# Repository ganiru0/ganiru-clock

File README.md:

# ganiru-clock
 my first HPS clock

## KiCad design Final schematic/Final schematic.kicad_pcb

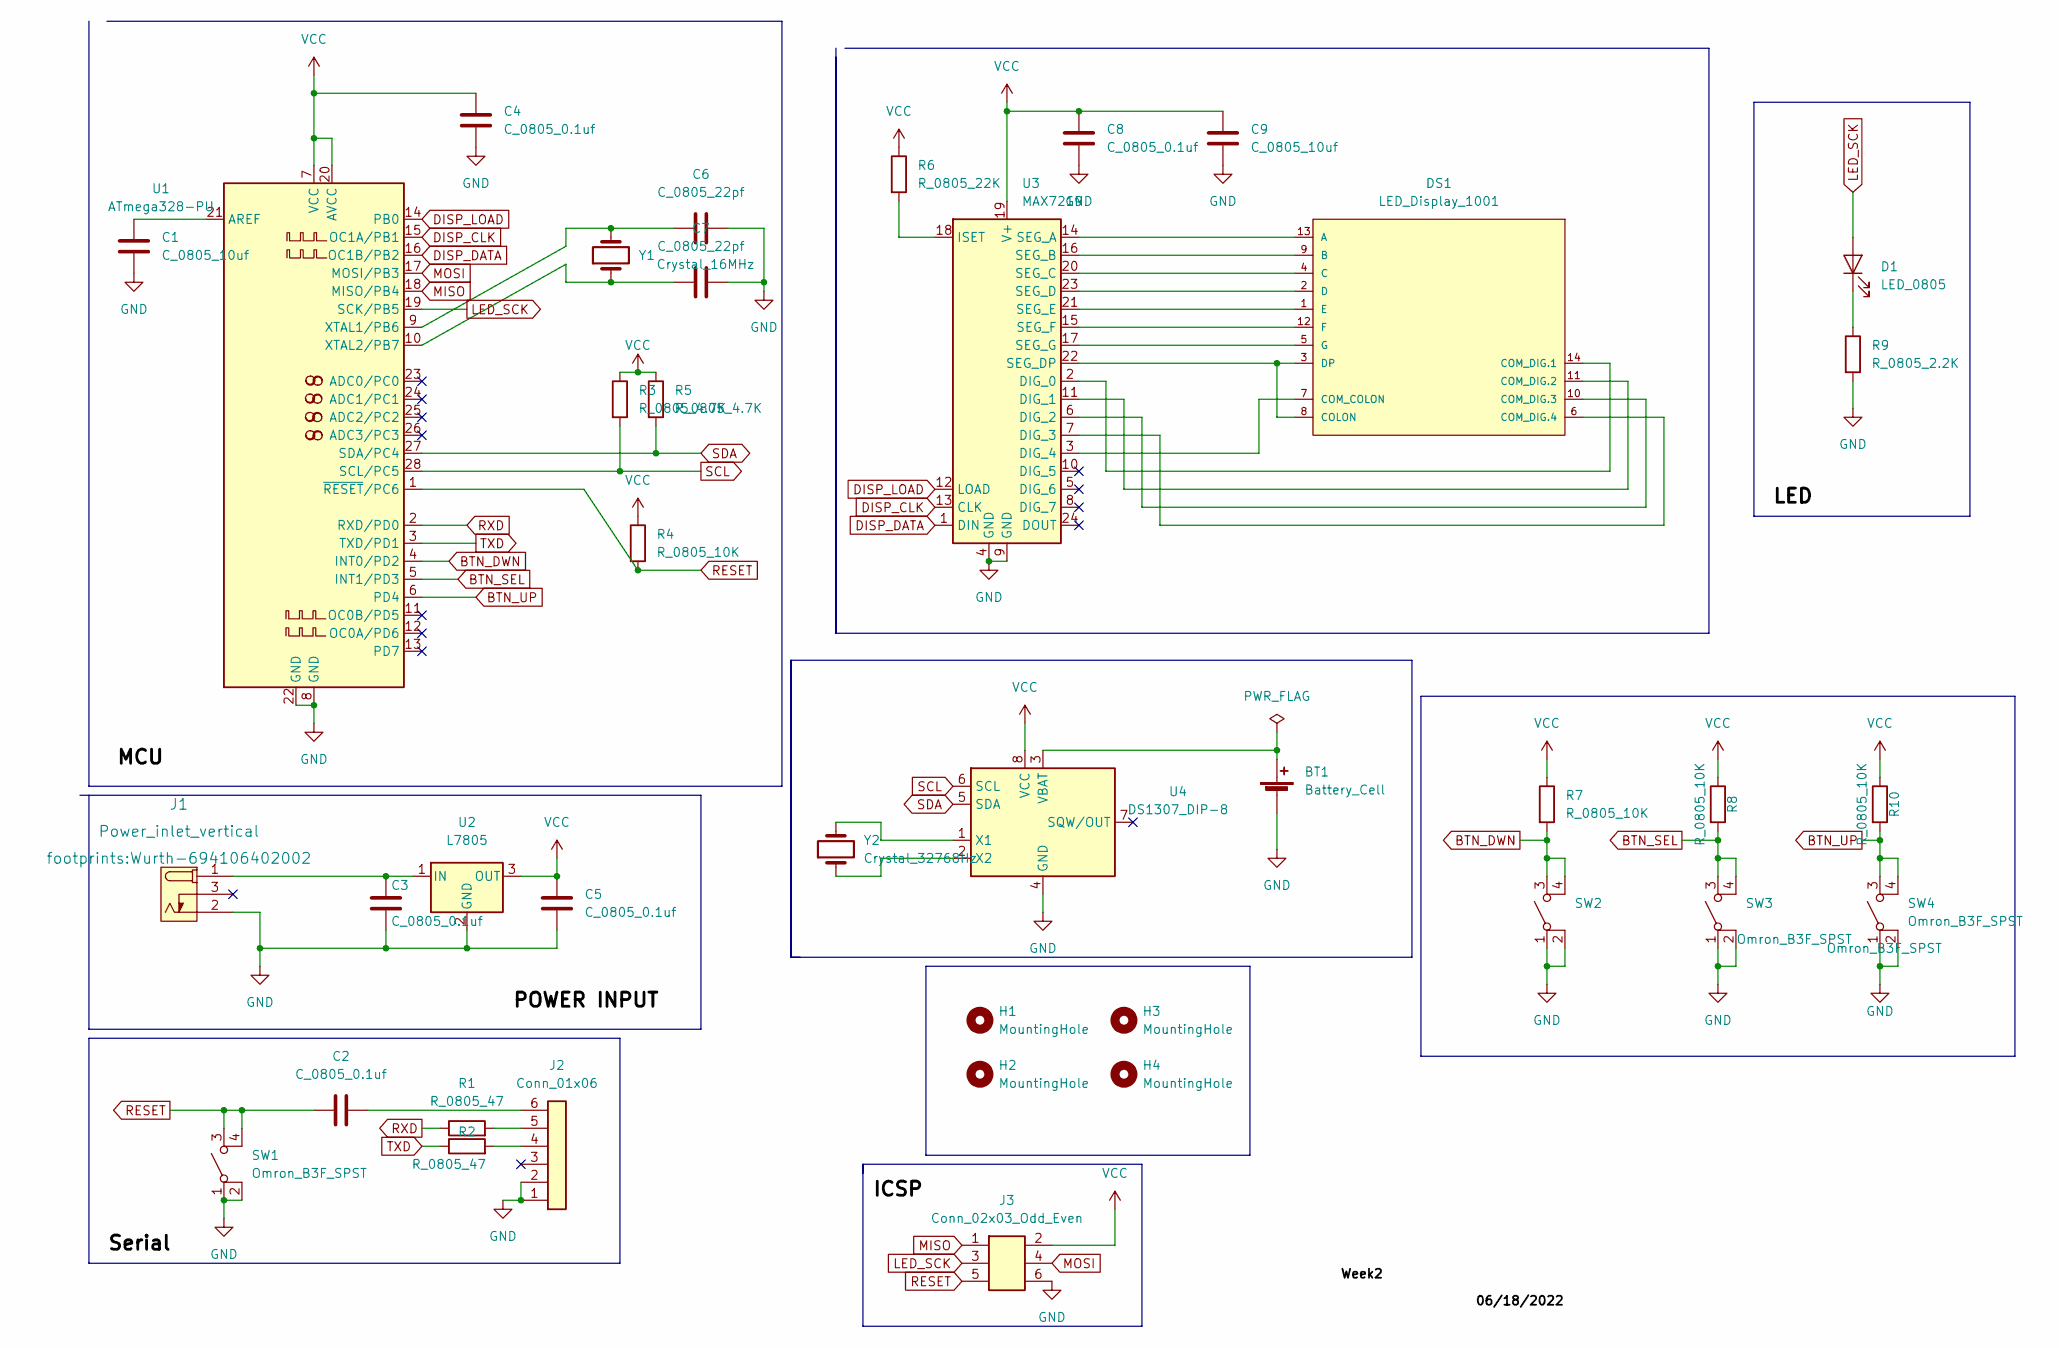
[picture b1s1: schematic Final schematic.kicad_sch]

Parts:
BT1: Battery_Cell; BatteryHolder_Keystone_106_1x20mm; MPN BS-7; Digikey PN BS-7-ND
C1, C9: C_0805_10uf; C_0805_2012Metric; Voltage N/A; Tolerance N/A; MPN GRM21BR61E106KA73L; Digikey PN 490-5523-1-ND
C2, C3, C4, C5, C8: C_0805_0.1uf; C_0805_2012Metric; Voltage N/A; Tolerance N/A; MPN 08055C104KAT2A; Digikey PN 478-1395-1-ND
C6, C7: C_0805_22pf; C_0805_2012Metric; Voltage N/A; Tolerance N/A; MPN CC0805JRNPO9BN220; Digikey PN 311-1103-1-ND
D1: LED_0805; LED_0805_2012Metric; MPN 150080RS75000; Digikey PN 732-4984-1-ND
DS1: LED_Display_1001; Adafruit-1001-0-0-MFG; forward voltage 3.2V; reverse voltage 5V; mouser part number 485-1001; digikey description WHITE 7-SEGMENT CLOCK DISPLAY
H1, H2, H3, H4: MountingHole; MountingHole_3.2mm_M3
J1: Power_inlet_vertical; Wurth-694106402002; MPN 694106402002; Digikey PN 732-5931-ND
J2: Conn_01x06; PinHeader_1x06_P2.54mm_Vertical; MPN 61300611121; Digikey PN 732-5319-ND
J3: Conn_02x03_Odd_Even; PinHeader_2x03_P2.54mm_Vertical; MPN PRPC003DAAN-RC; Digikey PN S2011EC-03-ND
R1, R2: R_0805_47; R_0805_2012Metric; Tolerance N/A; Mouser PN N/A; Digikey PN RC0805FR-0747RL
R3, R5: R_0805_4.7K; R_0805_2012Metric; Tolerance N/A; MPN RC0805FR-074K7L; Digikey PN 311-4.70KCRCT-ND
R4, R7, R8, R10: R_0805_10K; R_0805_2012Metric; Tolerance N/A; MPN RC0805FR-0710KL; Digikey PN 311-10.0KCRCT-ND
R6: R_0805_22K; R_0805_2012Metric; Tolerance N/A; MPN RC0805FR-0722KL; Digikey PN 311-22.0KCRCT-ND
R9: R_0805_2.2K; R_0805_2012Metric; Tolerance N/A; MPN N/A; Digikey PN 311-2.20KCRCT-ND
SW1, SW2, SW3, SW4: Omron_B3F_SPST; SW_SPST_Omron_B3FS-100xP; MPN B3FS-1000P; Digikey PN SW423CT-ND
U1: ATmega328-PU; DIP-28_W7.62mm; MPN ED281DT; Digikey PN ED3050-5-ND
U2: L7805; TO-252-2; MPN L7805CDT-TR; Digikey PN 497-7255-1-ND
U3: MAX7219; DIP-24_W7.62mm; MPN ED241DT; Digikey PN ED3049-5-ND
U4: DS1307_DIP-8; DIP-8_W7.62mm; MPN A 08-LC-TT; Digikey PN AE9986-ND
Y1: Crystal_16MHz; Crystal_SMD_HC49-SD; MPN ECS-160-20-5PXDN-TR; Digikey PN XC1299CT-ND
Y2: Crystal_32768Hz; Crystal_SMD_2Pin_3.2x1.5mm; MPN Q 0,032768-JTX310-12,5-20-T1-HMR-50K-LF; Digikey PN 1908-1314-1-ND

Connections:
BTN_DWN: R7.2, SW2.3 (B), SW2.4 (B), U1.4 (INT0/PD2)
BTN_SEL: R8.2, SW3.3 (B), SW3.4 (B), U1.5 (INT1/PD3)
BTN_UP: R10.2, SW4.3 (B), SW4.4 (B), U1.6 (PD4)
DISP_CLK: U1.15 (OC1A/PB1), U3.13 (CLK)
DISP_DATA: U1.16 (OC1B/PB2), U3.1 (DIN)
DISP_LOAD: U1.14 (PB0), U3.12 (LOAD)
GND: BT1.2 (-), C1.2, C3.2, C4.2, C5.1, C6.2, C7.2, C8.1, C9.2, J1.2 (OUT), J2.1, J2.2, J3.6, R9.2, SW1.1 (A), SW1.2 (A), SW2.1 (A), SW2.2 (A), SW3.1 (A), SW3.2 (A), SW4.1 (A), SW4.2 (A), U1.8 (GND), U1.22 (GND), U2.2 (GND), U3.4 (GND), U3.9 (GND), U4.4 (GND)
LED_SCK: D1.2 (A), J3.3, U1.19 (SCK/PB5)
MISO: J3.1, U1.18 (MISO/PB4)
MOSI: J3.4, U1.17 (MOSI/PB3)
unnamed: BT1.1 (+), U4.3 (VBAT)
unnamed: C1.1, U1.21 (AREF)
unnamed: C2.2, J2.6
unnamed: C3.1, J1.1 (POLE), U2.1 (IN)
unnamed: C6.1, U1.9 (XTAL1/PB6), Y1.2
unnamed: C7.1, U1.10 (XTAL2/PB7), Y1.1
unnamed: D1.1 (K), R9.1
unnamed: DS1.1 (E), U3.21 (SEG_E)
unnamed: DS1.2 (D), U3.23 (SEG_D)
unnamed: DS1.3 (DP), DS1.8 (COLON), U3.22 (SEG_DP)
unnamed: DS1.4 (C), U3.20 (SEG_C)
unnamed: DS1.5 (G), U3.17 (SEG_G)
unnamed: DS1.6 (COM_DIG.4), U3.7 (DIG_3)
unnamed: DS1.7 (COM_COLON), U3.3 (DIG_4)
unnamed: DS1.9 (B), U3.16 (SEG_B)
unnamed: DS1.10 (COM_DIG.3), U3.6 (DIG_2)
unnamed: DS1.11 (COM_DIG.2), U3.11 (DIG_1)
unnamed: DS1.12 (F), U3.15 (SEG_F)
unnamed: DS1.13 (A), U3.14 (SEG_A)
unnamed: DS1.14 (COM_DIG.1), U3.2 (DIG_0)
unnamed: J2.4, R2.2
unnamed: J2.5, R1.2
unnamed: R6.2, U3.18 (ISET)
unnamed: U4.1 (X1), Y2.2
unnamed: U4.2 (X2), Y2.1
RESET: C2.1, J3.5, R4.2, SW1.3 (B), SW1.4 (B), U1.1 (~RESET/PC6)
RXD: R1.1, U1.2 (RXD/PD0)
SCL: R3.2, U1.28 (SCL/PC5), U4.6 (SCL)
SDA: R5.2, U1.27 (SDA/PC4), U4.5 (SDA)
TXD: R2.1, U1.3 (TXD/PD1)
VCC: C4.1, C5.2, C8.2, C9.1, J3.2, R3.1, R4.1, R5.1, R6.1, R7.1, R8.1, R10.1, U1.7 (VCC), U1.20 (AVCC), U2.3 (OUT), U3.19 (V+), U4.8 (VCC)

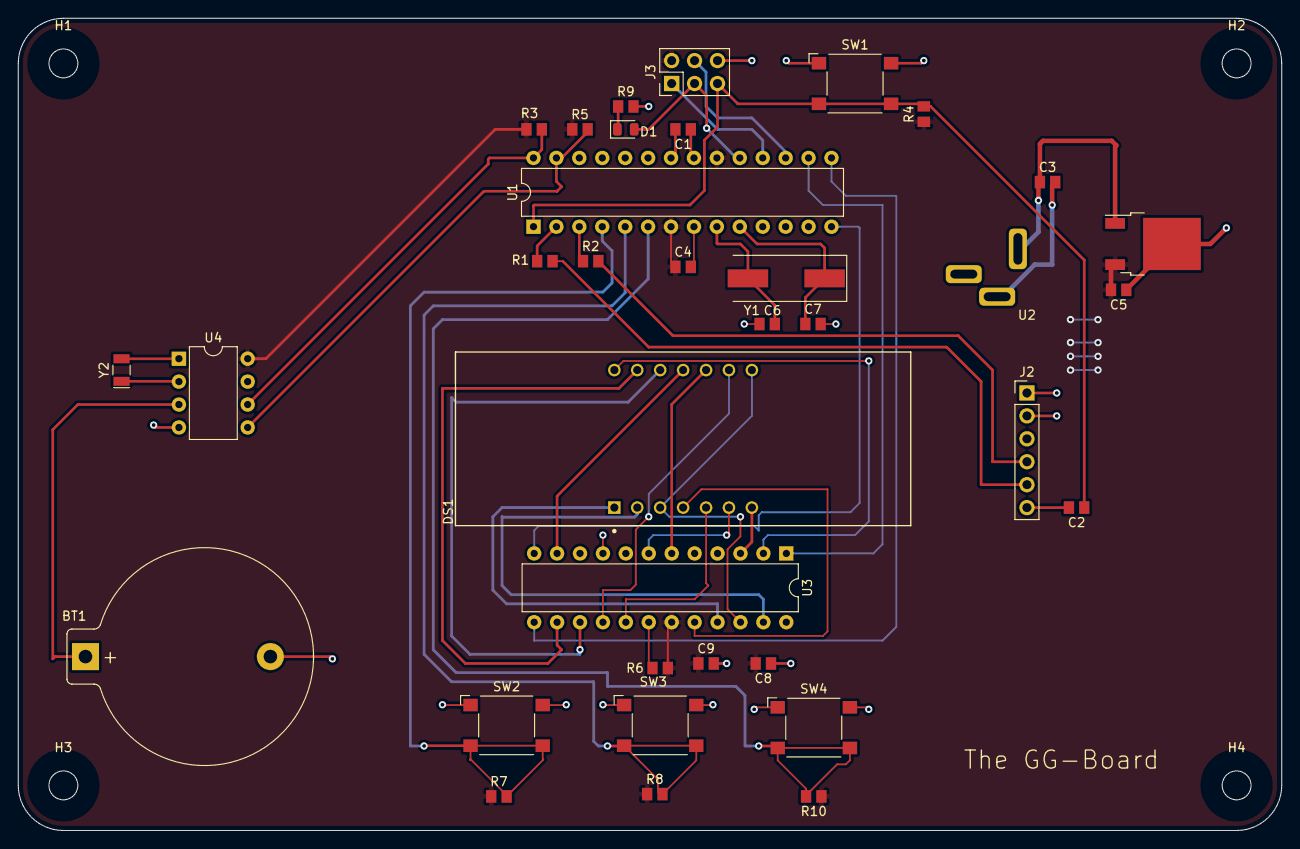
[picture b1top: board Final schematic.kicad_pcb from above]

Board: 2 copper layers, 140.0 x 90.0 mm, 39 parts (1 on the bottom side), 41 nets.

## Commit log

2022-06-13 Create week1
2022-06-13 Create blink video
2022-06-13 Create napkin sketch
2022-06-19 Update Blink video
2022-06-19 Update napkin sketch
2022-06-21 adding weeks 1 and 2
2022-07-15 schematic review
2022-07-16 more edits
2022-07-18 pcb update
2022-07-18 pdb update
2022-07-20 schematic update
2022-07-21 pcb update
    pcb update
2022-07-26 A few updates before manufacturing
    Hi Ganiru, just fixing a few small things on the board and schematic before we send it for manufacturing.
2022-07-26 One last change
    updating pours to 0.3/0.3
2022-07-26 gerber out
